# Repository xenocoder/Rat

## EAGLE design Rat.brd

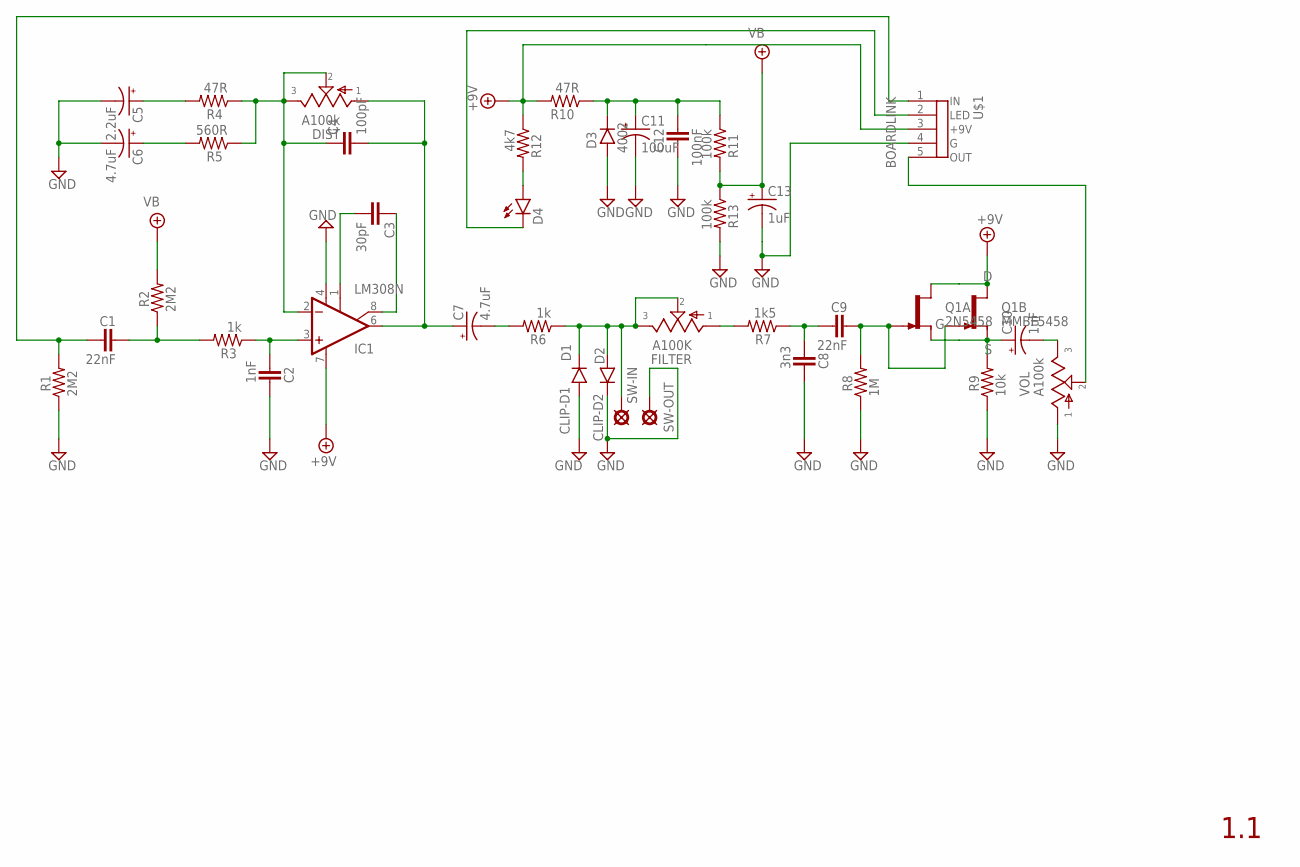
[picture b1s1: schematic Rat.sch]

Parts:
C1, C9: 22nF; 072X025
C2: 1nF; 072X025
C3: 30pF; 050X030_025
C4: 100pF; 050X030_025
C5: 2.2uF; 050_020_1
C6, C7: 4.7uF; 050_020_1
C8: 3n3; 072X025
C10, C13: 1uF; 050_020_1
C11: 100uF; 080_035_1
C12: 100nF; 072X025
D1: CLIP-D1; DO35-3
D2: CLIP-D2; DO35-3
D3: 4002; DO41-3
D4: LED3MM
DIST: A100k; 16MM
FILTER: A100K; 16MM
IC1: LM308N; DIL08
Q1A: 2N5458; TO92-
Q1B: MMBF5458; SOT23
R1, R2: 2M2; R0207/3
R3, R6: 1k; R0207/3
R4, R10: 47R; R0207/3
R5: 560R; R0207/3
R7: 1k5; R0207/3
R8: 1M; R0207/3
R9: 10k; R0207/3
R11, R13: 100k; R0207/3
R12: 4k7; R0207/3
SW-IN: PAD; SQUARE
SW-OUT: PADO; ROUND
U$1: BOARDLINK
VOL: A100k; 16MM

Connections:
+9V: IC1.7 (V+), Q1A.3 (D), Q1B.1 (D), R10.2, R12.1, U$1.3 (+9V)
GND: C2.2, C5.-, C6.-, C8.2, C11.-, C12.1, C13.-, D1.A, D2.C, D3.A, IC1.4 (V-), R1.1, R8.1, R9.1, R13.2, SW-OUT.1, U$1.4 (G), VOL.1
unnamed: C1.2, R2.1, R3.2
unnamed: C2.1, IC1.3 (+IN), R3.1
unnamed: D4.A, R12.2
unnamed: C5.+, R4.2
unnamed: C6.+, R5.2
unnamed: C4.1, DIST.2, DIST.3, IC1.2 (-IN), R4.1, R5.1
unnamed: C3.2, IC1.1 (CMP1)
unnamed: C3.1, IC1.8 (CMP2)
unnamed: C4.2, C7.+, DIST.1, IC1.6 (OUT)
unnamed: C7.-, R6.2
unnamed: D1.C, D2.A, FILTER.2, FILTER.3, R6.1, SW-IN.1
unnamed: C8.1, C9.1, R7.1
unnamed: C9.2, Q1A.1 (G), Q1B.3 (G), R8.2
unnamed: FILTER.1, R7.2
unnamed: C10.+, Q1A.2 (S), Q1B.2 (S), R9.2
unnamed: C10.-, VOL.3
unnamed: D4.K (C), U$1.2 (LED)
unnamed: C1.1, R1.2, U$1.1 (IN)
unnamed: U$1.5 (OUT), VOL.2
unnamed: C11.+, C12.2, D3.C, R10.1, R11.1
VB: C13.+, R2.2, R11.2, R13.1

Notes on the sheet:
1.1

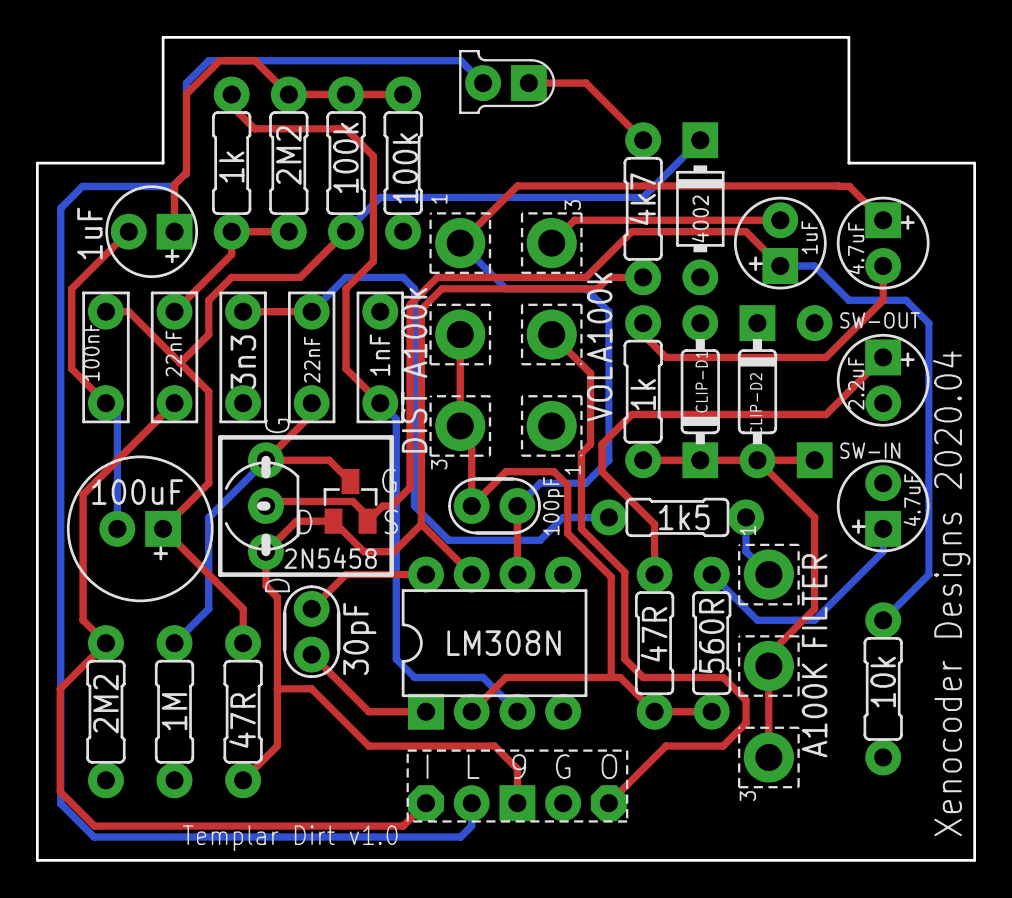
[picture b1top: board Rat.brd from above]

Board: 2 copper layers, 52.1 x 45.7 mm, 39 parts (0 on the bottom side), 23 nets.

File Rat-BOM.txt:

Partlist exported from /Users/evanhowell/git/Rat/Rat.sch at 10/18/18 6:22 PM

Part   Value     Device       Package     Description          
C1     22nF      072X0252     072X025     1000pF - 0.47uF      
C2     1nF       072X0252     072X025     1000pF - 0.47uF      
C3     30pF      050X030_0251 050X030_025 47 - 120pF           
C4     100pF     050X030_0251 050X030_025 47 - 120pF           
C5     2.2uF     0501         050_020_1   0.22 - 100uF         
C6     4.7uF     0501         050_020_1   0.22 - 100uF         
C7     4.7uF     0501         050_020_1   0.22 - 100uF         
C8     3n3       072X0252     072X025     1000pF - 0.47uF      
C9     22nF      072X0252     072X025     1000pF - 0.47uF      
C10    1uF       0501         050_020_1   0.22 - 100uF         
C11    100uF     0801         080_035_1   47 - 470uF           
C12    100nF     072X0252     072X025     1000pF - 0.47uF      
C13    1uF       0501         050_020_1   0.22 - 100uF         
D1     1N914     1N914.3      DO35-3      Fast Switching Diode 
D2     1N914     1N914.3      DO35-3      Fast Switching Diode 
D3     4002      1N400X.3     DO41-3      Rectifier Diodes     
D4     LED3MM    LED3MM       LED3MM                           
DIST   A100k     POT16MM      16MM        Potentiometers       
FILTER A100K     POT16MM      16MM        Potentiometers       
IC1    LM308N    LM308N       DIL08       OP AMP               
Q1A    2N5458    2N5458       TO92-       N-CHANNEL JFET       
Q1B    MMBF5458  MMBF5458     SOT23       SMD 5458             
R1     2M2       6MM.3        R0207/3     6mm Resistors        
R2     2M2       6MM.3        R0207/3     6mm Resistors        
R3     1k        6MM.3        R0207/3     6mm Resistors        
R4     47R       6MM.3        R0207/3     6mm Resistors        
R5     560R      6MM.3        R0207/3     6mm Resistors        
R6     1k        6MM.3        R0207/3     6mm Resistors        
R7     1k5       6MM.3        R0207/3     6mm Resistors        
R8     1M        6MM.3        R0207/3     6mm Resistors        
R9     10k       6MM.3        R0207/3     6mm Resistors        
R10    47R       6MM.3        R0207/3     6mm Resistors        
R11    100k      6MM.3        R0207/3     6mm Resistors        
R12    4k7       6MM.3        R0207/3     6mm Resistors        
R13    100k      6MM.3        R0207/3     6mm Resistors        
U$1    BOARDLINK BOARDLINK    BOARDLINK                        
VOL    A100k     POT16MM      16MM        Potentiometers

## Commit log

2018-10-19 First version that went to Seeed Studio
2018-11-17 Updated SOT23 footprint to right connections
2018-11-24 Fixed issue of SMD 5458
2018-12-12 Files for Seeed Studio
2018-12-12 Files to Seeed Studio
2020-01-17 Update RAT-1590B-DrillGuide.ai
    Added Rat Drill Guide
2025-11-22 Updated BOM
